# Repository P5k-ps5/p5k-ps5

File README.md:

# p5k-ps5

**Web: [p5k-ps5.github.io](https://p5k-ps5.github.io)** · Licencia [GPL-3.0](LICENSE)

Una placa abierta que va entre tu DualSense y la PS5 (a través de un adaptador P5Mate) y aplica tu perfil
(sticks, gatillos, botones, turbo, macros, anti-recoil y ayuda al apuntado) mil veces por segundo, ajustable desde
el móvil por WiFi.

```
DualSense --USB--> placa p5k-ps5 (MAX3421E + ESP32-S3) --USB--> P5Mate --> PS5
                                    `--WiFi--> la app en el móvil
```

| Carpeta | Qué hay |
|---|---|
| `main/`, `components/motor/` | Firmware del ESP32-S3 (ESP-IDF) y el motor en Rust que aplica el perfil |
| `placa/` | La placa propia: esquema, PCB y archivos de fabricación para JLCPCB ([LEEME](placa/LEEME.md)) |
| `caja/` | Cajas impresas en 3D para el montaje con módulos ([LEEME](caja/LEEME.md)) |
| `escritorio/` | App de escritorio (Windows y macOS): graba el firmware y puede hacer de puente |
| `app/` | App nativa de macOS (SwiftUI) |
| `web/` | La web del proyecto (se publica en p5k-ps5.github.io) |

> **Anti-recoil y ayuda al apuntado: solo para modos sin conexión** (campaña, zombis, partidas contra bots). En
> partidas online es hacer trampas y el anti-trampas lo detecta; usarlos ahí puede costarte la cuenta.

Originalmente el puente era el Mac en medio:

```
DualSense --Bluetooth--> app del Mac --serie--> ESP32-S3 --USB--> consola (con un adaptador con licencia)
```

## Firmware

Firmware para una placa ESP32-S3 (probado en una GERUI ESP32-S3 WROOM-1 N16R8 DevKitC-1) que se presenta
por USB como un **mando de PS4** (DualShock 4, VID `054C`, PID `09CC`) y envía su estado a 1000 Hz.
El estado del mando le llega desde un ordenador por el puerto serie, o con órdenes de texto para probarlo.

## Qué hace
- **USB nativo → mando de PS4** (TinyUSB, HID). Responde a las peticiones de configuración habituales
  (calibración, tipo de mando, dirección, versión). **No** contesta a la autenticación de PS4/PS5: para
  usarlo en una consola hace falta un adaptador con licencia que se encargue de eso.
- **Dos modos**, guardados en memoria:
  - `mac`: mando + puerto serie por el mismo cable USB (para probar con el ordenador).
  - `consola`: solo mando.
- **LED RGB (GPIO48)**: rojo = sin conectar · verde = conectado en modo mac · cian = conectado en modo
  consola · destello azul = el aparato ha pedido datos de configuración.
- **Botón BOOT**: pulsación corta = botón ✕ · mantener 2 s = cambiar de modo.

## Tramas del ordenador
Por el puerto serie (el «COM» a 921600 baudios, o el puerto serie USB en modo mac):

```
A5 5A | botones (2 bytes, bajo primero) | cruceta | lx | ly | rx | ry | l2 | r2 | XOR de esos 9 bytes
```

- Botones en el orden de bits del DualShock 4: □ ✕ ○ △ L1 R1 L2 R2 Share Options L3 R3 PS táctil.
- Cruceta: 0 = arriba y en sentido horario hasta 7; 8 = suelta.
- Sticks y gatillos de 0 a 255 (128 = centro de los sticks).
- Si dejan de llegar tramas durante 250 ms, el mando vuelve al centro.

## La placa sin ordenador
Con un DualSense conectado por USB a un MAX3421E (host USB por SPI), la placa hace lo mismo que la app
de escritorio, sin ordenador: aplica el perfil (anti-recoil, ayuda al apuntado, turbo, macros, sticks,
gatillos, botones…) y sirve **la misma app web por WiFi**. El motor es el mismo código Rust que la app de
escritorio (`components/motor`). La WiFi tiene onboarding: si no hay red de casa configurada (o deja de
funcionar), la placa abre su propia red, **p5k-ps5 XXXX**, y el móvil abre la página solo al
conectarse. En casa, la placa está en **http://puente.local**. Detalles y API en `PLACA-WEB.md`.

```
DualSense --USB--> MAX3421E --SPI--> ESP32-S3 (motor + app web) --USB--> PS5 (modo dualsense)
                                                                      --> P5Mate --> consola (modo consola)
```

## Órdenes de texto (por el mismo puerto)
`ayuda`, `pulsa <botón> [ms]`, `manten <botón>`, `suelta [botón]`, `stick <izq|der> <x> <y>`,
`gatillo <l2|r2> <0-100>`, `demo`, `estado` (modo, WiFi y clave de la app web), `modo <mac|consola|dualsense>`,
`wifi` (estado y redes), `wifi buscar`, `wifi olvidar` (abre la red propia), `medir` (cuánto tarda el
motor), `grabar` (reinicia en modo grabación), `reinicia`.

## Compilar y grabar
Con ESP-IDF 5.5 y la toolchain de Rust para el ESP32-S3 (el motor, `components/motor`, se compila con
cargo durante `idf.py build`):

```bash
cargo install espup --locked && espup install --targets esp32s3   # una vez
idf.py set-target esp32s3
idf.py build
idf.py -p /dev/cu.usbmodemXXXX flash monitor
```

Las pruebas del motor se ejecutan en el ordenador: `cd components/motor && cargo +stable test --target aarch64-apple-darwin --lib`.
Con la placa ya en marcha, el firmware también se puede actualizar por WiFi desde la pestaña Placa
(`build/puente_mando.bin`).

Si la placa está en el USB nativo con este firmware, entra en modo grabación con la orden `grabar` (o
manteniendo BOOT y pulsando RST) y, tras grabar, reinicia con `--after watchdog_reset` en esptool.

## App de macOS

App nativa en SwiftUI (macOS 13 o posterior). No hace falta Xcode: basta con las herramientas de
línea de órdenes de Apple.

```bash
./construir_app.sh      # crea «p5k-ps5.app» en esta carpeta
./ejecutar_pruebas.sh   # pruebas automáticas del motor
```

- Lee el DualSense con el framework GameController y aplica el perfil activo unas 1000 veces por
  segundo: sticks, gatillos, reasignación, turbo, macros, anti-recoil y ayuda al apuntado.
- Perfiles guardados en `~/Library/Application Support/Puente de mando/perfiles.json`.
- Servidor web local, solo para la red de casa y protegido con clave, para ver y ajustar todo desde el móvil.
- «Mi control»: mide tu propio stick mientras disparas, para practicar.
- `mac/prueba_mando.py` comprueba desde el Mac que la placa responde como mando (necesita `hidapi` y `pyserial`).

Pensada para modos sin conexión. En partidas online, usar anti-recoil o macros es hacer trampas y los
anti-trampas lo detectan.

## App de escritorio (Windows y macOS)

Carpeta `escritorio/` (Tauri 2: Rust + interfaz web). Es el **puente completo**, sin necesitar el Mac:

- Lee el DualSense (USB o Bluetooth), aplica el perfil activo (sticks, gatillos, botones, turbo, macros,
  anti-recoil fijo, progresivo o por patrón, ayuda al apuntado, widgets y combinaciones del mando) unas 1000 veces
  por segundo y lo manda a la ESP32. El procesador es un port de `app/Procesador.swift` y da la misma salida byte a
  byte (`cargo test --lib procesador`, con los casos que genera `src-tauri/pruebas/generar.sh` desde el de Swift).
- Usa el mismo `perfiles.json` que la app de Mac (en Windows, en `%APPDATA%\Puente de mando`).
- Sirve la misma página que el móvil y el iPad (sacada de `app/Pagina.swift` al compilar) en el puerto 8787; la
  ventana de la app es esa misma página. Avisos con la voz del sistema o en pantalla.
- Al abrirla por primera vez guía para grabar el firmware en la ESP32-S3 y comprar el **P5Mate**; el menú «Puente»
  lleva al panel, al asistente del firmware y a la dirección para el móvil.

```bash
cd escritorio && npm install
npm run dev                 # la app en modo desarrollo (necesita Rust)
npm run build               # instalador del sistema en el que estés (.dmg en Mac)
./construir_windows.sh      # instalador de Windows (.exe) desde el Mac
```

Tiene todo lo de la app de Mac: también «Mi control», el monitor de la señal y las secciones Móvil y Ayuda. Para probar la app nueva junto a la de Mac sin tocar nada suyo: `PUENTE_ARCHIVO`
(otra copia de los perfiles), `PUENTE_PUERTO` (otro puerto) y `PUENTE_SIN_PLACA=1` (no abrir la placa). No abras
las dos apps a la vez con la placa: las dos le mandarían el mando.

En Windows, la primera vez el cortafuegos pregunta si deja entrar conexiones: permite las **redes privadas** para
que el móvil y el iPad puedan abrir el panel. Sin firmar, Windows enseña el aviso de SmartScreen («Más información
→ Ejecutar de todas formas»).

## Licencia
Todo el proyecto (firmware, apps, placa, caja y web) se publica con la licencia
[GNU GPL v3](LICENSE). Las fuentes Inter Tight y Geist Mono tienen su propia licencia, la SIL Open Font
License 1.1 (viaja dentro de cada fuente).

Proyecto personal, sin relación con Sony Interactive Entertainment. PlayStation, PS5 y DualSense son marcas de
sus dueños.

## Créditos
El descriptor HID y las respuestas de configuración del DualShock 4 están basados en
[GP2040-CE](https://github.com/OpenStickCommunity/GP2040-CE) (licencia MIT, OpenStickCommunity).

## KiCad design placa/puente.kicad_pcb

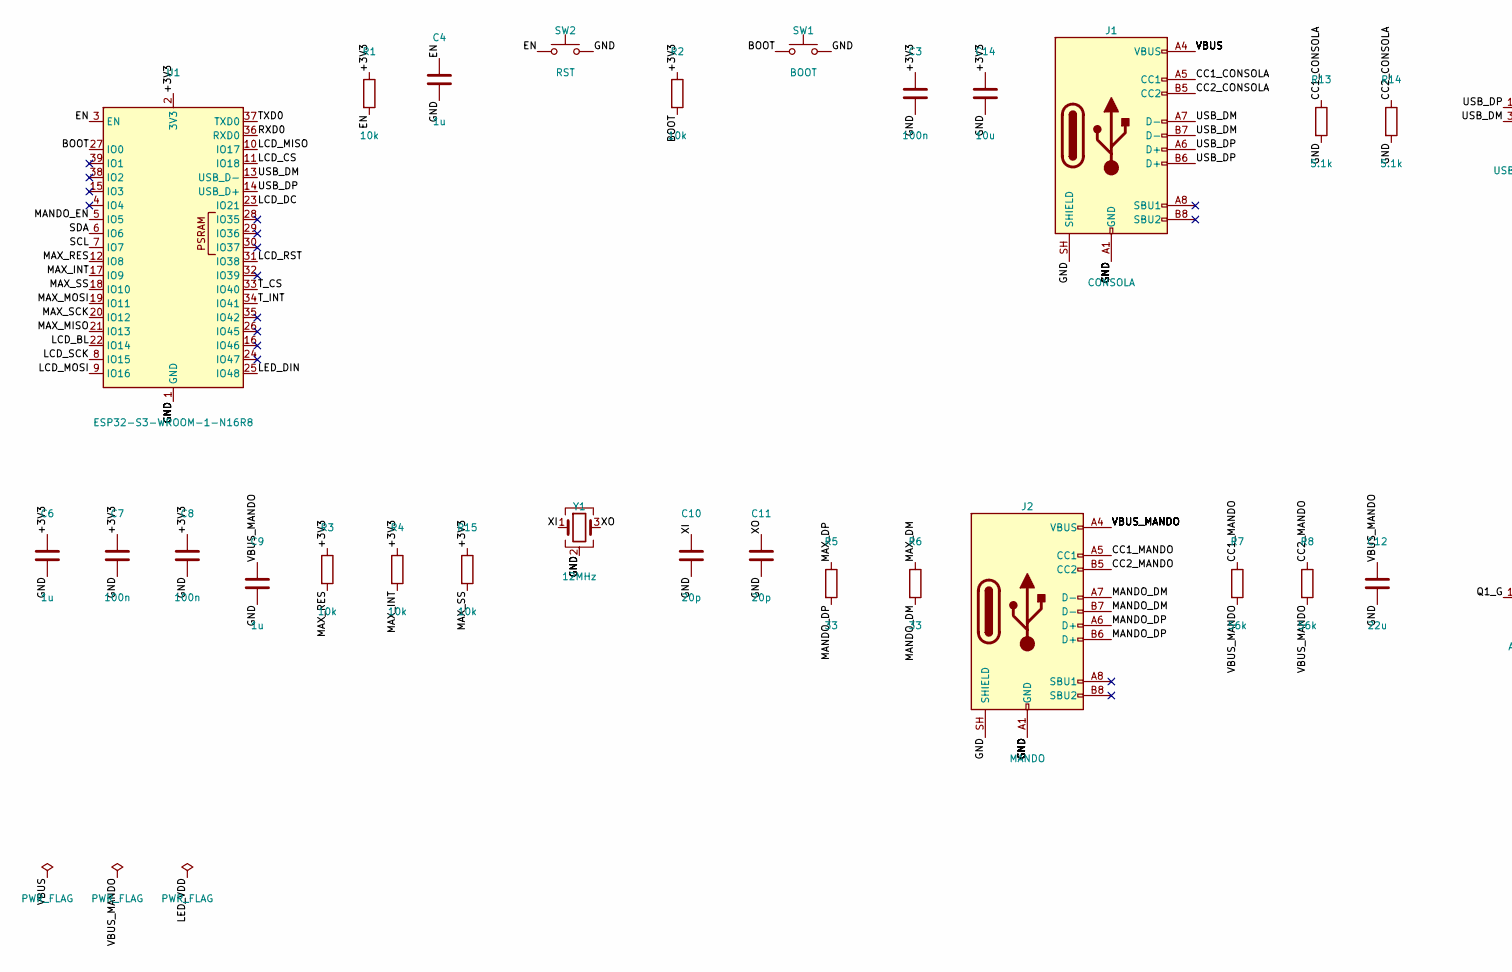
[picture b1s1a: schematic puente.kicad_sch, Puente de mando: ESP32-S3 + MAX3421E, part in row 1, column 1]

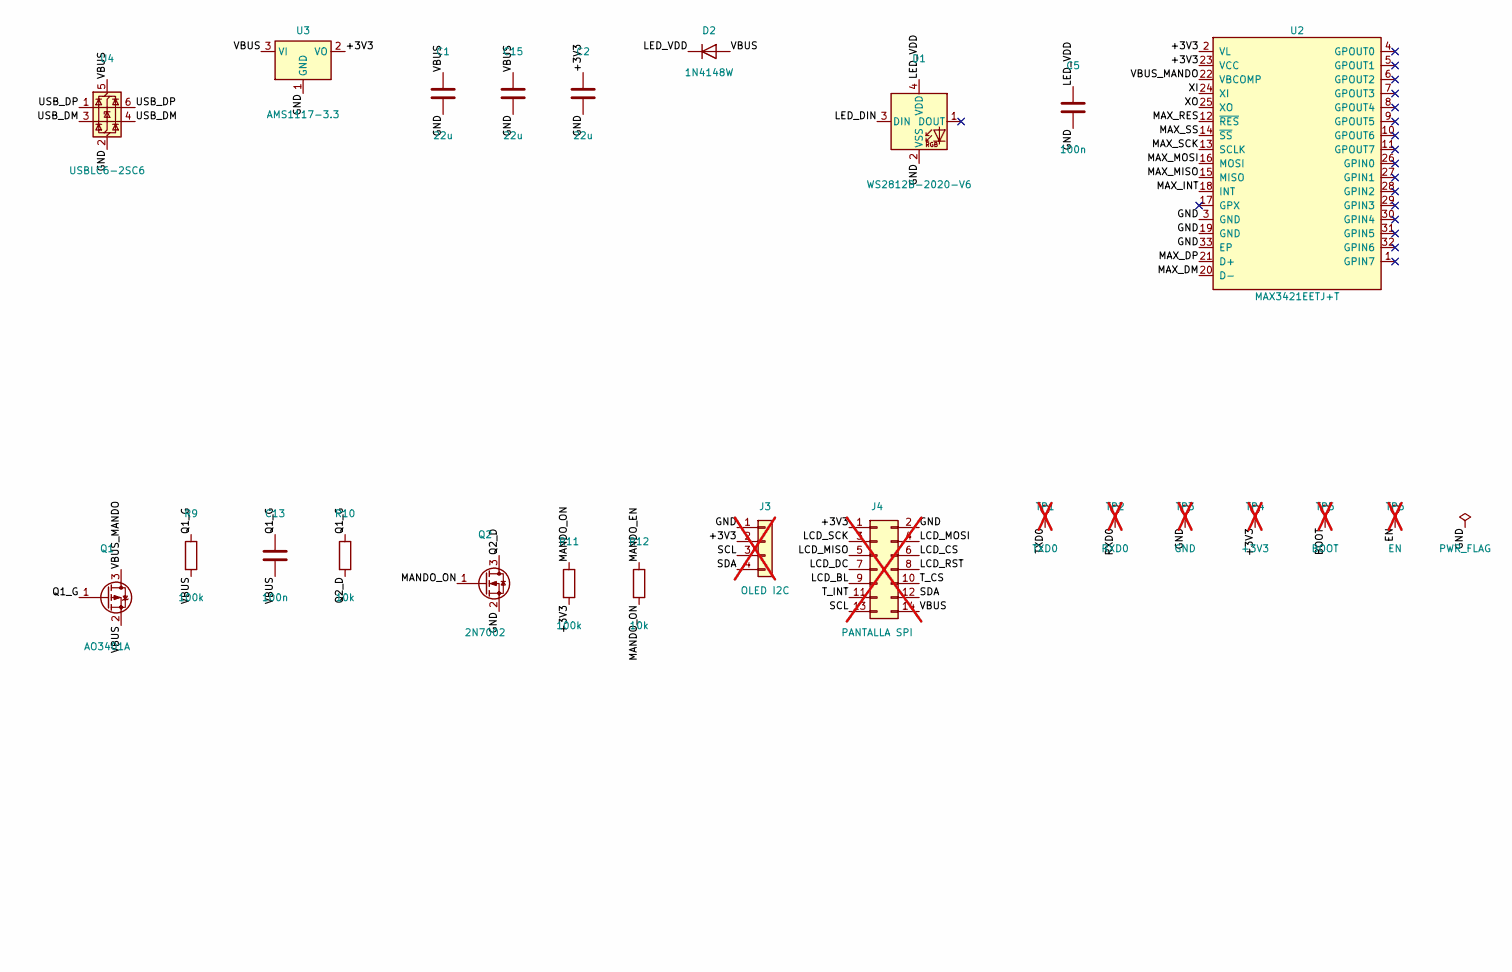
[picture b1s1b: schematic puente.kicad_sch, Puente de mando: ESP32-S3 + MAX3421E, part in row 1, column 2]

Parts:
C1, C2, C12, C15: 22u; C_0805_2012Metric; LCSC C45783
C3, C5, C7, C8, C13: 100n; C_0402_1005Metric; LCSC C1525
C4, C6, C9: 1u; C_0402_1005Metric; LCSC C52923
C10, C11: 20p; C_0402_1005Metric; LCSC C1554
C14: 10u; C_0603_1608Metric; LCSC C19702
D1: WS2812B-2020-V6; LED_WS2812B-2020_PLCC4_2.0x2.0mm; LCSC C52917434
D2: 1N4148W; D_SOD-123; LCSC C81598
J1: CONSOLA; USB_C_Receptacle_HRO_TYPE-C-31-M-12; LCSC C165948
J2: MANDO; USB_C_Receptacle_HRO_TYPE-C-31-M-12; LCSC C165948
J3: OLED I2C; PinHeader_1x04_P2.54mm_Vertical; not fitted
J4: PANTALLA SPI; PinHeader_2x07_P2.54mm_Vertical; not fitted
Q1: AO3401A; SOT-23; LCSC C15127
Q2: 2N7002; SOT-23; LCSC C8545
R1, R2, R3, R4, R10, R12, R15: 10k; R_0402_1005Metric; LCSC C25744
R5, R6: 33; R_0402_1005Metric; LCSC C25105
R7, R8: 56k; R_0402_1005Metric; LCSC C25796
R9, R11: 100k; R_0402_1005Metric; LCSC C25741
R13, R14: 5.1k; R_0402_1005Metric; LCSC C25905
SW1: BOOT; SW_Push_1P1T_XKB_TS-1187A; LCSC C318884
SW2: RST; SW_Push_1P1T_XKB_TS-1187A; LCSC C318884
TP1: TXD0; TestPoint_Pad_D1.0mm; not fitted
TP2: RXD0; TestPoint_Pad_D1.0mm; not fitted
TP3: GND; TestPoint_Pad_D1.0mm; not fitted
TP4: +3V3; TestPoint_Pad_D1.0mm; not fitted
TP5: BOOT; TestPoint_Pad_D1.0mm; not fitted
TP6: EN; TestPoint_Pad_D1.0mm; not fitted
U1: ESP32-S3-WROOM-1-N16R8; ESP32-S3-WROOM-1; LCSC C2913202
U2: MAX3421EETJ+T; TQFN-32-1EP_5x5mm_P0.5mm_EP3.1x3.1mm; LCSC C1870151
U3: AMS1117-3.3; SOT-223-3_TabPin2; LCSC C6186
U4: USBLC6-2SC6; SOT-23-6; LCSC C7519
Y1: 12MHz; Crystal_SMD_3225-4Pin_3.2x2.5mm; LCSC C9002

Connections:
/+3V3: C2.1, C3.1, C6.1, C7.1, C8.1, C14.1, J3.2, J4.1, R1.1, R2.1, R3.1, R4.1, R11.2, R15.1, TP4.1, U1.2 (3V3), U2.2 (VL), U2.23 (VCC), U3.2 (VO)
/BOOT: R2.2, SW1.1, TP5.1, U1.27 (IO0)
/CC1_CONSOLA: J1.A5 (CC1), R13.1
/CC1_MANDO: J2.A5 (CC1), R7.1
/CC2_CONSOLA: J1.B5 (CC2), R14.1
/CC2_MANDO: J2.B5 (CC2), R8.1
/EN: C4.1, R1.2, SW2.1, TP6.1, U1.3 (EN)
/GND: C1.2, C2.2, C3.2, C4.2, C5.2, C6.2, C7.2, C8.2, C9.2, C10.2, C11.2, C12.2, C14.2, C15.2, D1.2 (VSS), J1.A1 (GND), J1.A12 (GND), J1.B1 (GND), J1.B12 (GND), J1.SH (SHIELD), J2.A1 (GND), J2.A12 (GND), J2.B1 (GND), J2.B12 (GND), J2.SH (SHIELD), J3.1, J4.2, Q2.2 (S), R13.2, R14.2, SW1.2, SW2.2, TP3.1, U1.1 (GND), U1.40 (GND), U1.41 (GND), U2.3 (GND), U2.19 (GND), U2.33 (EP), U3.1 (GND), U4.2 (GND), Y1.2 (G), Y1.4 (G)
/LCD_BL: J4.9, U1.22 (IO14)
/LCD_CS: J4.6, U1.11 (IO18)
/LCD_DC: J4.7, U1.23 (IO21)
/LCD_MISO: J4.5, U1.10 (IO17)
/LCD_MOSI: J4.4, U1.9 (IO16)
/LCD_RST: J4.8, U1.31 (IO38)
/LCD_SCK: J4.3, U1.8 (IO15)
/LED_DIN: D1.3 (DIN), U1.25 (IO48)
/LED_VDD: C5.1, D1.4 (VDD), D2.1 (K)
/MANDO_DM: J2.A7 (D-), J2.B7 (D-), R6.2
/MANDO_DP: J2.A6 (D+), J2.B6 (D+), R5.2
/MANDO_EN: R12.1, U1.5 (IO5)
/MANDO_ON: Q2.1 (G), R11.1, R12.2
/MAX_DM: R6.1, U2.20 (D-)
/MAX_DP: R5.1, U2.21 (D+)
/MAX_INT: R4.2, U1.17 (IO9), U2.18 (INT)
/MAX_MISO: U1.21 (IO13), U2.15 (MISO)
/MAX_MOSI: U1.19 (IO11), U2.16 (MOSI)
/MAX_RES: R3.2, U1.12 (IO8), U2.12 (~RES)
/MAX_SCK: U1.20 (IO12), U2.13 (SCLK)
/MAX_SS: R15.2, U1.18 (IO10), U2.14 (~SS)
/Q1_G: C13.1, Q1.1 (G), R9.1, R10.1
/Q2_D: Q2.3 (D), R10.2
/RXD0: TP2.1, U1.36 (RXD0)
/SCL: J3.3, J4.13, U1.7 (IO7)
/SDA: J3.4, J4.12, U1.6 (IO6)
/TXD0: TP1.1, U1.37 (TXD0)
/T_CS: J4.10, U1.33 (IO40)
/T_INT: J4.11, U1.34 (IO41)
/USB_DM: J1.A7 (D-), J1.B7 (D-), U1.13 (USB_D-), U4.3 (I/O2), U4.4 (I/O2)
/USB_DP: J1.A6 (D+), J1.B6 (D+), U1.14 (USB_D+), U4.1 (I/O1), U4.6 (I/O1)
/VBUS: C1.1, C13.2, C15.1, D2.2 (A), J1.A4 (VBUS), J1.A9 (VBUS), J1.B4 (VBUS), J1.B9 (VBUS), J4.14, Q1.2 (S), R9.2, U3.3 (VI), U4.5 (VBUS)
/VBUS_MANDO: C9.1, C12.1, J2.A4 (VBUS), J2.A9 (VBUS), J2.B4 (VBUS), J2.B9 (VBUS), Q1.3 (D), R7.2, R8.2, U2.22 (VBCOMP)
/XI: C10.1, U2.24 (XI), Y1.1
/XO: C11.1, U2.25 (XO), Y1.3

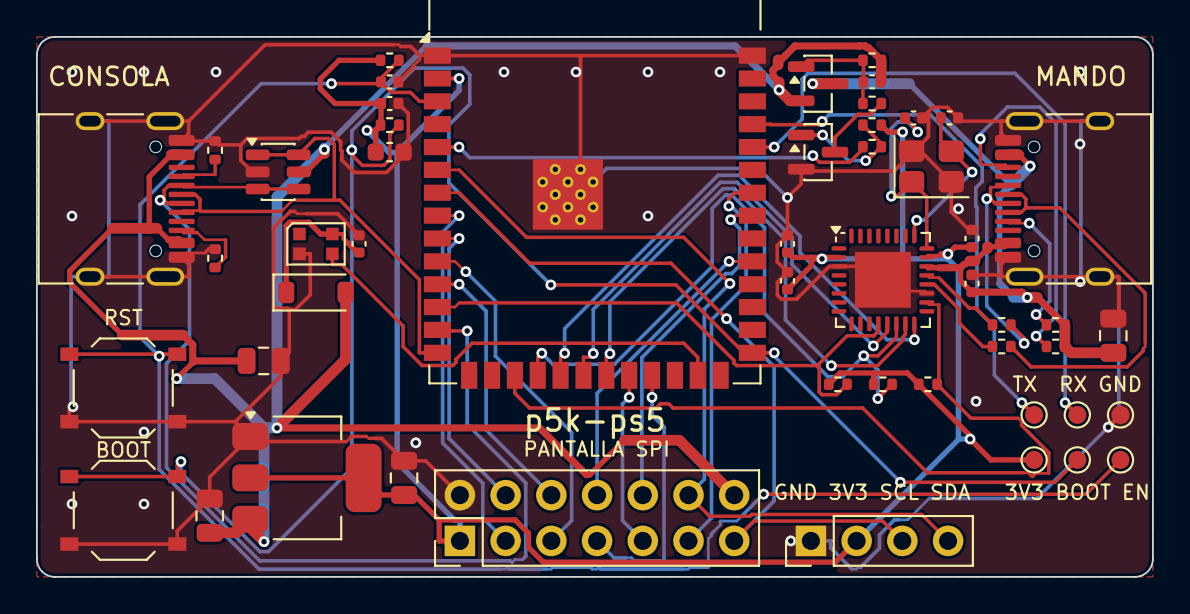
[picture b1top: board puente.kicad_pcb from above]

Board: 2 copper layers, 62.0 x 30.0 mm, 51 parts (0 on the bottom side), 43 nets.

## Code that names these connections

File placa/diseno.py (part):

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    R("R13", "5.1k", "CC1_CONSOLA", "GND", LCSC["R5k1"]),
    R("R14", "5.1k", "CC2_CONSOLA", "GND", LCSC["R5k1"]),
    dict(ref="U4", sym="Power_Protection:USBLC6-2SC6", valor="USBLC6-2SC6", fp="Package_TO_SOT_SMD:SOT-23-6",
         lcsc="C7519", pines={"1": "USB_DP", "6": "USB_DP", "3": "USB_DM", "4": "USB_DM", "2": "GND", "5": "VBUS"}),
    dict(ref="U3", sym="Regulator_Linear:AMS1117-3.3", valor="AMS1117-3.3", fp="Package_TO_SOT_SMD:SOT-223-3_TabPin2",
         lcsc="C6186", pines={"1": "GND", "2": "+3V3", "3": "VBUS"}),
    C("C1", "22u", "VBUS", "GND", LCSC["C22u"], "Capacitor_SMD:C_0805_2012Metric"),
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
    # --- LED RGB (a 5 V menos un diodo: así entiende los 3,3 V del ESP32) ---
    dict(ref="D2", sym="Diode:1N4148W", valor="1N4148W", fp="Diode_SMD:D_SOD-123", lcsc="C81598",
         pines={"1": "LED_VDD", "2": "VBUS"}),
    dict(ref="D1", sym="LED:WS2812B-2020", valor="WS2812B-2020-V6", fp="LED_SMD:LED_WS2812B-2020_PLCC4_2.0x2.0mm",
         lcsc="C52917434", pines={"2": "GND", "3": "LED_DIN", "4": "LED_VDD"}),
    C("C5", "100n", "LED_VDD", "GND", LCSC["C100n"]),

    # --- MAX3421E ---
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
    # --- Interruptor del VBUS del mando, con arranque suave (evita el bajón al enchufar el mando en caliente) ---
    dict(ref="Q1", sym="Transistor_FET:AO3401A", valor="AO3401A", fp="Package_TO_SOT_SMD:SOT-23",
         lcsc="C15127", pines={"1": "Q1_G", "2": "VBUS", "3": "VBUS_MANDO"}),
    R("R9", "100k", "Q1_G", "VBUS", LCSC["R100k"]),
    C("C13", "100n", "Q1_G", "VBUS", LCSC["C100n"]),
    R("R10", "10k", "Q1_G", "Q2_D", LCSC["R10k"]),
    dict(ref="Q2", sym="Transistor_FET:2N7002", valor="2N7002", fp="Package_TO_SOT_SMD:SOT-23",
         lcsc="C8545", pines={"1": "MANDO_ON", "2": "GND", "3": "Q2_D"}),
    R("R11", "100k", "MANDO_ON", "+3V3", LCSC["R100k"]),
    R("R12", "10k", "MANDO_EN", "MANDO_ON", LCSC["R10k"]),

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         pines={"1": "GND", "2": "+3V3", "3": "SCL", "4": "SDA"}),
    dict(ref="J4", sym="Connector_Generic:Conn_02x07_Odd_Even", valor="PANTALLA SPI", dnp=True,
         fp="Connector_PinHeader_2.54mm:PinHeader_2x07_P2.54mm_Vertical", lcsc="",
         pines={"1": "+3V3", "2": "GND", "3": "LCD_SCK", "4": "LCD_MOSI", "5": "LCD_MISO", "6": "LCD_CS",
                "7": "LCD_DC", "8": "LCD_RST", "9": "LCD_BL", "10": "T_CS", "11": "T_INT", "12": "SDA",
                "13": "SCL", "14": "VBUS"}),

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

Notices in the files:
placa/puente.kicad_pcb:
GPL-3.0 · placa rev 1
